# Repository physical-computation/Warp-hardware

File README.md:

**The Warp hardware platform integrates 21 sensors in a complete system that is 3.6cmx3.3cm**
- - - - 

# Warp
Warp is a hardware platform for efficient multi-modal sensing with adaptive approximation. The hardware contains 11 sensor integrated circuits (ICs) and a total of 21 different sensors. The design includes circuit-level facilities for trading sensor accuracy for power dissipation, and circuit-level facilities for trading sensor communication reliability for power dissipation. The sensors in Warp cover eight sensing modalities: temperature, pressure, 3-axis acceleration, 3-axis angular velocity, 3-axis magnetic flux density, humidity, infrared, color/light (615nm, 525nm, 465nm).

## Prerequisites
We provide the hardware design files in the Eagle CAD format. You can use the free version of Eagle for MacOS, Linux, Windows to view the files. The design is a 10-layer PCB. You will need the full version of Eagle to make modifications. [For academics, the full version of Eagle (Eagle Professional) is completely free](https://knowledge.autodesk.com/support/eagle/learn-explore/caas/sfdcarticles/sfdcarticles/Eagle-Education.html). For non-university hobbyists, Eagle is relatively inexpensive and can also be purchased on a month-at-a-time subscription.

We also provide the hardware design files as Gerbers. You can use any of the numerous free Gerber viewers to view the design.

## Getting boards manufactured
The repository contains detailed instructions for getting the boards manufactured. We provide a pre-populated BOM file with part numbers for purchasing the components from Mouser. Before getting your own boards manufactured, it is worthwhile getting in touch with us for a brief discussion of things to be careful about in providing instructions to your board assembly house.

## Adapting the designs
We license the Warp hardware designs under a BSD license. See details in [LICENSE.txt](https://github.com/physical-computation/Warp-hardware/blob/master/LICENSE.txt).

## Generating Gerbers for manufacturing
The repository comes with the Gerber files pre-generated. You can generate your own Gerber files and drill files for manufacturing using Eagle.

## Getting boards assembled
Basic [BOM](https://github.com/physical-computation/Warp-hardware/blob/master/revA/bom/mouser/warp-revA-bom.xlsx) (uses Mouser for components).

# Implementation and Debug

# Mechanical CAD Models for Board and Enclosures
The repository also contains a mechanical CAD model for the board and designs for enclosures, in Autodesk Fusion 360 format. [For academics, the full version of Autodesk Fusion 360 is completely free](https://www.autodesk.co.uk/products/fusion-360/students-teachers-educators). For non-university hobbyists, Fusion 360 is relatively inexpensive and can be purchased on a month-at-a-time subscription.

## Getting firmware
You can obtain baseline firmware for the Warp platform from the [Warp firmware](https://github.com/physical-computation/Warp-firmware) repository.

## Bugs
See the GitHub issues for a complete list. Before getting your own boards manufactured, it is worthwhile getting in touch with us for a brief discussion of things to be careful about in providing instructions to your board assembly house and hints for getting the firmware running on Warp for the first time.

### If you use Warp in your research, please cite it as:
Phillip Stanley-Marbell and Martin Rinard. “A Hardware Platform for Efficient Multi-Modal Sensing with Adaptive Approximation”. ArXiv e-prints (2018). arXiv:1804.09241.

**BibTeX:**
```
@ARTICLE{1804.09241,
	author = {Stanley-Marbell, Phillip and Rinard, Martin},
	title = {A Hardware Platform for Efficient Multi-Modal 
	Sensing with Adaptive Approximation},
	journal = {ArXiv e-prints},
	archivePrefix = {arXiv},
	eprint = {1804.09241},
	year = 2018,
}
```
Phillip Stanley-Marbell and Martin Rinard. “Warp: A Hardware Platform for Efficient Multi-Modal Sensing with Adaptive Approximation”. IEEE Micro, Volume 40 , Issue 1 , Jan.-Feb. 2020.

**BibTeX:**
```
@ARTICLE{8959350,
	author = {P. {Stanley-Marbell} and M. {Rinard}}, 
	title = {Warp: A Hardware Platform for Efficient Multi-Modal
	Sensing with Adaptive Approximation},
	journal = {IEEE Micro},
	year = {2020}, 
	volume = {40}, 
	number = {1}, 
	pages = {57-66}, 
	ISSN = {1937-4143}, 
	month = {Jan},
}
```
### Acknowledgements
This research is supported by an Alan Turing Institute award TU/B/000096 under EPSRC grant EP/N510129/1, by Royal Society grant RG170136, and by EPSRC grants EP/P001246/1 and EP/R022534/1.

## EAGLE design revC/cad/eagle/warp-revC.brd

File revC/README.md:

## Overview
Warp Revision C adds support for a replaceable battery on a JST-PH connector, battery charging via USB, and a new Bluetooth LE module.

## Switch Settings
- Switch S1: Position 1: OFF; Position 2: OFF
- Switch S2: Position 1, OFF; Position 2: ON

## Battery
JST-PH connector. Polarity: When looking at the top surface of the Warp Revision C board (surface with logo and serial number), the red (positive) conductor will be on the left and the black (negative) conductor will be on the right:

## Connecting via Bluetooth LE
You can connect to Warp using the BGX Commander app on [iOS](https://apps.apple.com/us/app/bgxcommander/id1350920514) and [Android](https://play.google.com/store/apps/details?id=com.silabs.bgxcommander&hl=en_GB&gl=US) (and using similar facilities on Linux, Windows, and macOS):

Once connected, select your Warp from the list of devices and you get a terminal into the Warp prompt (or if your firmware is compiled to enable `WARP_BUILD_BOOT_TO_CSVSTREAM`, you get the CSV stream):

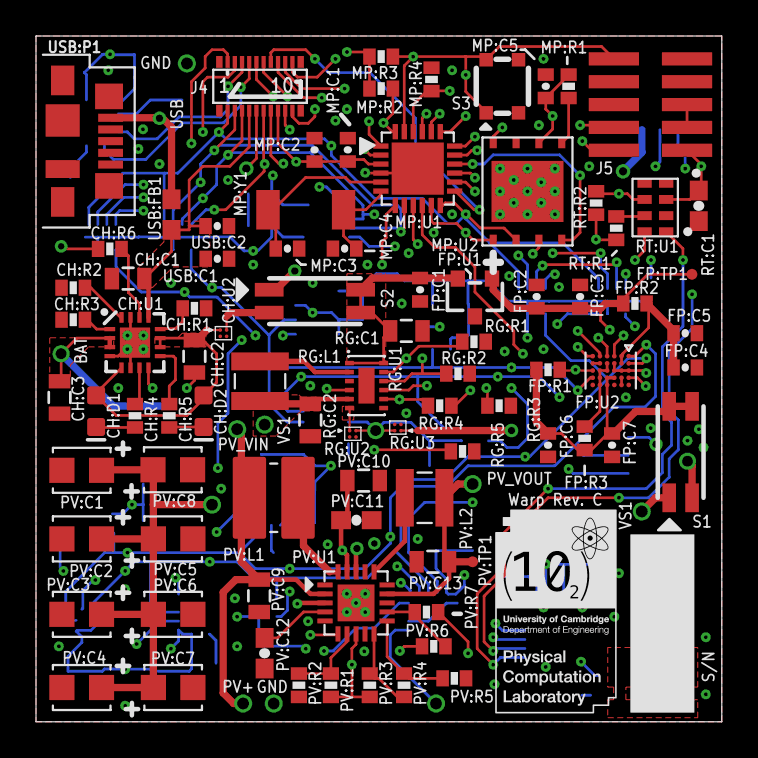
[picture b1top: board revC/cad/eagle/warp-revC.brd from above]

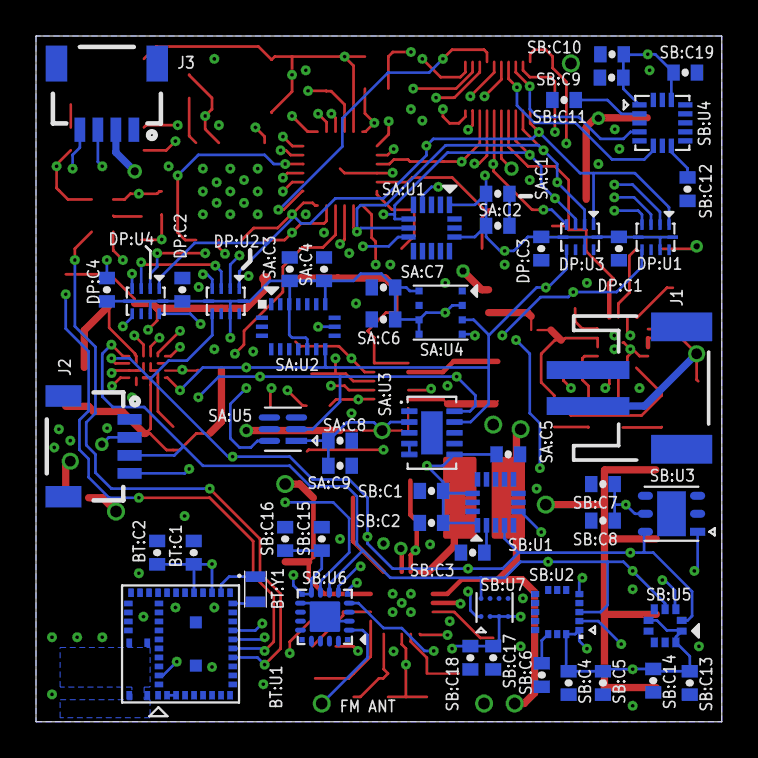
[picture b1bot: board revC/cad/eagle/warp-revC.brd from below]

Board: 10 copper layers, 38.1 x 38.1 mm, 141 parts (55 on the bottom side), 73 nets.

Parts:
BT:C1: 0.1uF; 0402-CAP
BT:C2: 1uF; 0402-CAP
BT:U1: BGX13S22GA-V21R; BGX13S
BT:Y1: IQXC-25
CH:C1: 1uF; 0805
CH:C2, CH:C3: 4.7uF; 0805
CH:D1: Green; LED-0603
CH:D2: Red; LED-0603
CH:R1: 2.94k; 0402-RES
CH:R2: 4.32k; 0402-RES
CH:R3: 10k; 0402-RES
CH:R4, CH:R5: 2k; 0402-RES
CH:R6: 56.2k; 0402-RES
CH:U1: BQ24230VQFN; PVQFN-N16
CH:U2: MAX40200; DSBGA
DP:C1, DP:C2, DP:C3, DP:C4: 0.1uF; 0402-CAP
DP:U1, DP:U2, DP:U3, DP:U4: ISL23415UTQFN; ISL23415
FP:C1, FP:C2: 1uF; 0402-CAP
FP:C3, FP:C4, FP:C7: 0.1uF; 0402-CAP
FP:C5, FP:C6: 10uF; 0402-CAP
FP:R1, FP:R3: 10k; 0402-RES
FP:R2: 100; 0402-RES
FP:TP1: TPSTP06R; TP06R
FP:U1: MCP1811AT-012/TTSOT-23-3; SOT23-3
FP:U2: ICE40UP5K-UWG30; LATTICE-WLCSP-30
J1: JST-2-SMD
J2, J3: QIIC connector; 1X04_1MM_RA
J4: DF40FC-20DP-0.4V(51); DF40C-20DP-0.4V(51)
J5: FTSH-105-01-XXX-DV-K
MP:C1, MP:C5: 0.1uF; 0402-CAP
MP:C2: 4.7uF; 0402-CAP
MP:C3, MP:C4: 33pF; 0402-CAP
MP:R1, MP:R2, MP:R4: 10k; 0402-RES
MP:R3: 4.7k; 0402-RES
MP:U1: MKL03Z32VFK4RQFN24; MKL03Z32VFK4R
MP:U2: AT45DB641E-MHN-Y; UDFN
MP:Y1: CM519-SMD; CM519
PV:C1, PV:C2, PV:C3, PV:C4, PV:C5, PV:C6, PV:C7, PV:C8: CPX3225A7552D; CPX3225A752D
PV:C9, PV:C10: 4.7uF; 0805
PV:C11: 0.1uF; 0603-CAP
PV:C12: 10nF; 0603-CAP
PV:C13: 22uF; 0805
PV:L1: 22uH; WE-TPC_3816
PV:L2: 10uH; WE-TPC_2811/2813_OLD
PV:R1: 4.02M; 0402-RES
PV:R2: 9.09M; 0402-RES
PV:R3: 1.3M; 0402-RES
PV:R4: 5.36M; 0402-RES
PV:R5: 6.49M; 0402-RES
PV:R6: 8.87M; 0402-RES
PV:R7: 4.22M; 0402-RES
PV:TP1: TPSTP06R; TP06R
PV:U1: BQ25570PVQFN; BQ25570
RG:C1, RG:C2: 10uF; 0805
RG:L1: 2.2uH; WE-TPC_2828_OLD
RG:R1, RG:R2, RG:R3, RG:R4, RG:R5: 2M; 0402-RES
RG:U1: TPS6274XWSON; WSON-12
RG:U2, RG:U3: MAX40200; DSBGA
RT:C1: 0.1uF; 0603-CAP
RT:R1, RT:R2: 10k; 0402-RES
RT:U1: RV-8803-C7_RTC; RV-C7
S1, S2: CHS-02_SWITCH
S3: EVPAYG0BAEVPAYG0BA; EVPAYG0BA
SA:C1, SA:C3, SA:C6, SA:C8: 0.1uF; 0402-CAP
SA:C2, SA:C4, SA:C7, SA:C9: 1uF; 0402-CAP
SA:C5: 4.7uF; 0402-CAP
SA:U1: ADXL362
SA:U2: BMX055
SA:U3: CCS811; SON60P270X400X110-11N
SA:U4: BME680LGA; BME680
SA:U5: TCS34725FN; TCS3772
SB:C1, SB:C3, SB:C4, SB:C7, SB:C9, SB:C11, SB:C12, SB:C13, SB:C16, SB:C17, SB:C19: 0.1uF; 0402-CAP
SB:C2, SB:C8, SB:C18: 1uF; 0402-CAP
SB:C5: 10uF; 0402-CAP
SB:C6: 10nF; 0402-CAP
SB:C10, SB:C14: 4.7uF; 0402-CAP
SB:C15: 22nF; 0402-CAP
SB:U1: MMA8451Q
SB:U2: L3GD20H
SB:U3: SI7021
SB:U4: FXOS8700CQ; QFN16
SB:U5: LPS25H
SB:U6: SI4705
SB:U7: HDC1000
USB:C1: 4.7uF; 0402-CAP
USB:C2: 0.1uF; 0402-CAP
USB:FB1: 600R/1A; 0603
USB:P1: MOLEX_USB_47346-0001MICRO_USB_B; USB-B-MICRO-SMD

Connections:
ADXL362_SPI_CS: MP:U1.P$15, SA:U1.P$8
BAT: CH:C3.1, CH:U1.2, CH:U1.3, J1.2
BGX13S_!RST: BT:U1.44, MP:U1.P$7
BOOST_VBAT: PV:C1.+, PV:C2.+, PV:C3.+, PV:C4.+, PV:C5.+, PV:C6.+, PV:C7.+, PV:C8.+, PV:U1.18
BT:N$1: BT:U1.21, BT:Y1.1
BT:N$2: BT:U1.19, BT:Y1.2
BT:N$3: BT:U1.2, BT:U1.3
CH:BQ24230_OUT: CH:C2.1, CH:D1.A, CH:D2.A, CH:U1.5, CH:U1.10, CH:U1.11, CH:U2.A1
CH:N$1: CH:R2.2, CH:U1.16
CH:N$2: CH:R1.2, CH:U1.12
CH:N$3: CH:R4.1, CH:U1.7
CH:N$4: CH:R3.2, CH:U1.1
CH:N$5: CH:R5.1, CH:U1.9
CH:N$6: CH:D1.C, CH:R4.2
CH:N$7: CH:D2.C, CH:R5.2
CH:N$8: CH:R6.2, CH:U1.14
CHARGE_VOUT: CH:U2.A2, S2.2
CLK32K: MP:U1.P$21, SB:U6.P$9
CRESET_B: FP:R1.1, FP:U2.F3, J4.P$17
FP:ICE40_VCC_PLL: FP:C4.1, FP:C5.1, FP:R2.1, FP:U2.B1, FP:U2.B2
FP:VCC_1V2: FP:C2.1, FP:C3.1, FP:R2.2, FP:TP1.TP, FP:U1.1, FP:U2.A3, FP:U2.B3, FP:U2.C2, FP:U2.C3
FP:VCC_SHUNT: FP:R3.1, FP:U2.D2, FP:U2.D3, FP:U2.E3, FP:U2.E4, FP:U2.E5
FPGA_CS: FP:U2.C1, J4.P$7, MP:U1.P$13
FPGA_VS: FP:C6.1, FP:C7.1, FP:R1.2, FP:R3.2, FP:U2.C4, FP:U2.D4, FP:U2.D5, S1.1', S1.2'
GND: BT:C1.2, BT:C2.2, BT:U1.1, BT:U1.4, BT:U1.5, BT:U1.20, BT:U1.31, BT:U1.45, BT:U1.46, BT:U1.47, BT:U1.48, BT:U1.49, BT:U1.50, BT:U1.51, CH:C1.2, CH:C2.2, CH:C3.2, CH:R1.1, CH:R2.1, CH:R3.1, CH:R6.1, CH:U1.4, CH:U1.6, CH:U1.8, CH:U1.15, CH:U1.EP, CH:U2.B2, DP:C1.2, DP:C2.2, DP:C3.2, DP:C4.2, DP:U1.9, DP:U2.9, DP:U3.9, DP:U4.9, FP:C1.2, FP:C2.2, FP:C3.2, FP:C4.2, FP:C5.2, FP:C6.2, FP:C7.2, FP:U1.3, FP:U2.B4, FP:U2.B5, FP:U2.E2, FP:U2.F2, J1.1, J2.1, J3.1, J4.P$20, J5.3, J5.5, MP:C1.2, MP:C2.2, MP:C3.2, MP:C4.2, MP:C5.2, MP:R4.2, MP:U1.P$4, MP:U1.P$PAD, MP:U2.7, MP:U2.9, PV:C1.-, PV:C2.-, PV:C3.-, PV:C4.-, PV:C5.-, PV:C6.-, PV:C7.-, PV:C8.-, PV:C9.2, PV:C10.2, PV:C11.2, PV:C12.2, PV:C13.2, PV:R2.1, PV:R5.1, PV:R7.1, PV:U1.1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
I2C0_SCL/UART_TX: BT:U1.14, J4.P$5, MP:U1.P$17, RT:U1.8
I2C0_SDA/UART_RX: BT:U1.13, J4.P$6, MP:U1.P$18, RT:U1.1
I2C1_SCL: DP:U1.6, FP:U2.A4, J3.4, J4.P$1, SA:U2.P$9, SA:U3.10, SA:U4.4, SA:U5.2
I2C1_SDA: DP:U3.6, FP:U2.F4, J3.3, J4.P$2, SA:U2.P$11, SA:U3.9, SA:U4.3, SA:U5.6
I2C2_SCL: DP:U2.6, FP:U2.A2, J2.4, J4.P$3, SB:U1.4, SB:U2.2, SB:U3.6, SB:U4.P$4, SB:U5.2, SB:U6.P$7, SB:U7.A1
I2C2_SDA: DP:U4.6, FP:U2.A1, J2.3, J4.P$4, SB:U1.6, SB:U2.3, SB:U3.1, SB:U4.P$6, SB:U5.4, SB:U6.P$8, SB:U7.A2
ISL23415_SPI_CS: DP:U1.4, DP:U2.4, DP:U3.4, DP:U4.4, J4.P$16, MP:U1.P$20
MP:AT45DB321F_SPI_CS: MP:U1.P$16, MP:U2.4
MP:EXTAL0: MP:C3.1, MP:U1.P$5, MP:Y1.P$1
MP:N$4: MP:R1.1, MP:U2.5
MP:XTAL0: MP:C4.1, MP:U1.P$6, MP:Y1.P$2
PV:LBOOST: PV:L1.2, PV:U1.20
PV:LBUCK: PV:L2.2, PV:U1.16
PV:OK_HYST: PV:R3.1, PV:R4.2, PV:U1.10
PV:OK_PROG: PV:R4.1, PV:R5.2, PV:U1.11
PV:VBAT_OV: PV:R1.1, PV:R2.2, PV:U1.7
PV:VOUT_SET: PV:R6.1, PV:R7.2, PV:U1.12
PV:VRDIV: PV:R1.2, PV:R3.2, PV:R6.2, PV:U1.8
PV:VREF_SAMP: PV:C12.1, PV:U1.4
PV:VSTOR: PV:C10.1, PV:C11.1, PV:U1.3, PV:U1.6, PV:U1.19
PV_VIN: J4.P$15, PV:C9.1, PV:L1.1, PV:U1.2
PV_VOUT: PV:C13.1, PV:L2.1, PV:TP1.TP, PV:U1.14, S2.1
REG_CTRL: MP:U1.P$19, RG:R5.2, RG:U1.4
REG_VIN: FP:C1.1, FP:U1.2, RG:C1.1, RG:U1.1, RG:U1.12, S2.1', S2.2'
REG_VSEL1: MP:U1.P$1, RG:R1.2, RG:U1.11
REG_VSEL2: MP:U1.P$2, RG:R2.2, RG:U1.10
REG_VSEL3: MP:U1.P$9, RG:R3.2, RG:U1.9
REG_VSEL4: MP:U1.P$10, RG:R4.2, RG:U1.8
RG:LOAD: RG:U1.6, RG:U2.A1
RG:SW: RG:L1.1, RG:U1.2
RT:N$3: RT:R1.1, RT:U1.7
RTC_!INT!/RESET_B: J4.P$10, J5.10, MP:R3.1, MP:U1.P$23, RT:R2.1, RT:U1.6, S3.A, S3.A'
SA:N$2: SA:U3.4, SA:U3.5
SB:CAP: SB:C6.1, SB:U2.14
SB:N$1: SB:C3.1, SB:U1.2
SB:N$2: SB:C11.1, SB:U4.P$2
SB:N$3: SB:C12.1, SB:U4.P$8
SI4705_!RST: MP:U1.P$14, SB:U6.P$5
SPI_MISO/UART_RTS: BT:U1.16, DP:U1.2, DP:U2.2, DP:U3.2, DP:U4.2, FP:U2.F1, J4.P$12, MP:U1.P$8, MP:U2.8, SA:U1.P$7
SPI_MOSI/UART_CTS: BT:U1.15, DP:U1.3, DP:U2.3, DP:U3.3, DP:U4.3, FP:U2.E1, J4.P$13, MP:U1.P$11, MP:U2.1, SA:U1.P$6
SPI_SCK: DP:U1.1, DP:U2.1, DP:U3.1, DP:U4.1, FP:U2.D1, J4.P$11, MP:U1.P$12, MP:U2.2, SA:U1.P$4
SWD_CLK: J4.P$9, J5.4, MP:R4.1, MP:U1.P$22
SWD_DIO: J4.P$8, J5.2, MP:R2.1, MP:U1.P$24
USB:VBUS: USB:FB1.2, USB:P1.1
USB_5V: CH:C1.1, CH:U1.13, J4.P$14, USB:C1.1, USB:C2.1, USB:FB1.1
VCC_QIIC: J2.2, J3.2, RG:U3.A1
VS1: J4.P$18, J5.1, MP:C1.1, MP:C2.1, MP:C5.1, MP:R1.2, MP:R2.2, MP:R3.2, MP:U1.P$3, MP:U2.3, MP:U2.6, RG:C2.1, RG:L1.2, RG:U1.5, RT:C1.1, RT:R1.2, RT:R2.2, RT:U1.3, S1.1
VS2: BT:C1.1, BT:C2.1, BT:U1.22, BT:U1.24, DP:C1.1, DP:C2.1, DP:C3.1, DP:C4.1, DP:U1.5, DP:U1.8, DP:U1.10, DP:U2.5, DP:U2.8, DP:U2.10, DP:U3.5, DP:U3.8, DP:U3.10, DP:U4.5, DP:U4.8, DP:U4.10, J4.P$19, RG:U2.A2, RG:U3.A2, S1.2, SA:C1.1, SA:C2.1, SA:C3.1, SA:C4.1, SA:C5.1, SA:C6.1, SA:C7.1, SA:C8.1, SA:C9.1, SA:U1.P$1, SA:U1.P$14, SA:U2.P$3, SA:U2.P$7, SA:U2.P$13, SA:U3.2, SA:U3.6, SA:U4.2, SA:U4.5, SA:U4.6, SA:U4.8, SA:U5.1, SB:C1.1, SB:C2.1, SB:C4.1, SB:C5.1, SB:C7.1, SB:C8.1, SB:C9.1, SB:C10.1, SB:C13.1, SB:C14.1, SB:C15.1, SB:C16.1, SB:C17.1, SB:C18.1, SB:C19.1, SB:U1.1, SB:U1.14, SB:U2.1, SB:U2.5, SB:U2.16, SB:U3.5, SB:U4.P$1, SB:U4.P$14, SB:U5.1, SB:U5.6, SB:U5.10, SB:U6.P$10, SB:U6.P$11, SB:U7.B1, SB:U7.C1, SB:U7.D1

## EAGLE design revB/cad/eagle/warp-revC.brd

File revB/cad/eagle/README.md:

# Warp revision B, Eagle CAD files

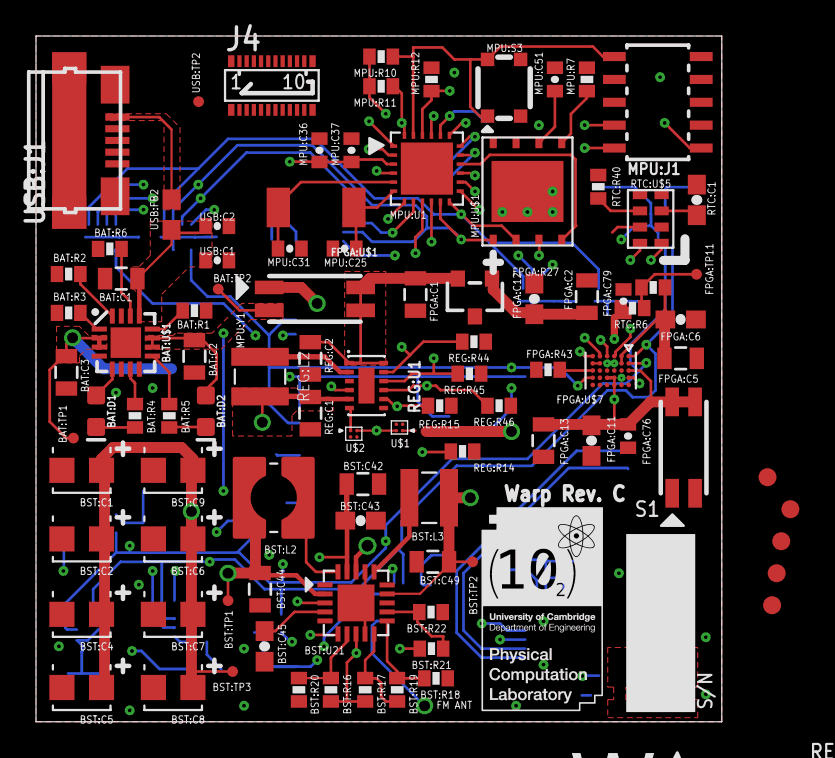
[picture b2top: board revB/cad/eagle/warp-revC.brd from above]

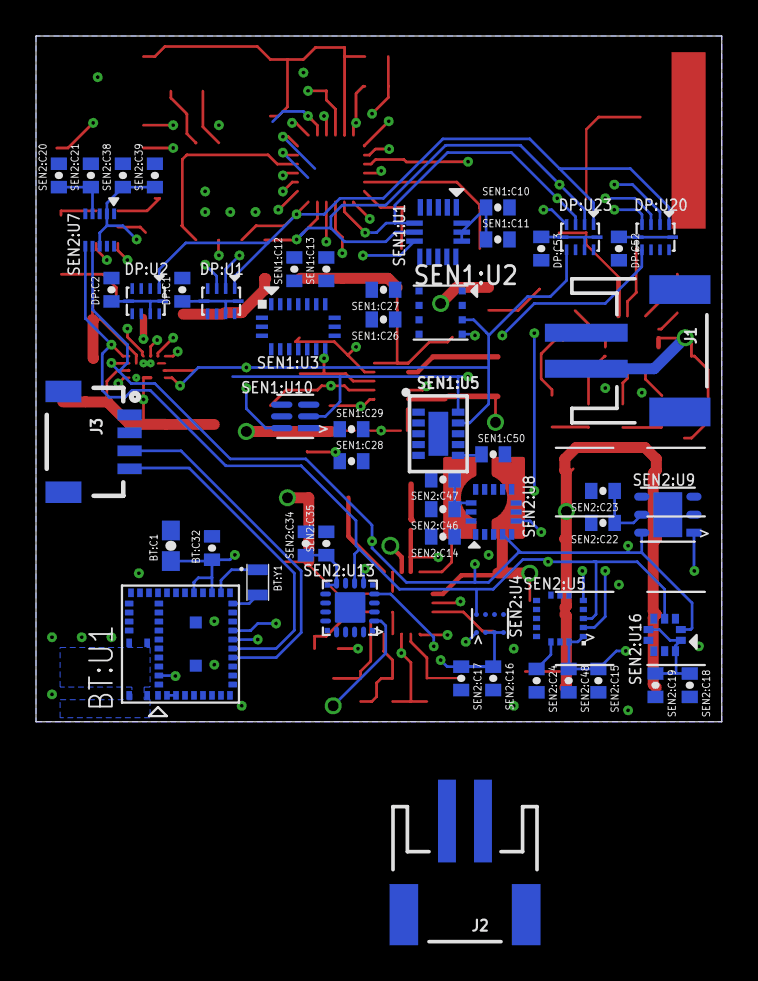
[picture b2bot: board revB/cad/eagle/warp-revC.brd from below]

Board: 10 copper layers, 38.1 x 38.1 mm, 150 parts (54 on the bottom side), 71 nets.

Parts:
BAT:C1: 1uF; 0805
BAT:C2, BAT:C3: 4.7uF; 0805
BAT:D1, BAT:D2: LED-0603
BAT:R1: 2.94k; 0402-RES
BAT:R2: 4.32k; 0402-RES
BAT:R3: 10k; 0402-RES
BAT:R4, BAT:R5: 4.7k; 0402-RES
BAT:R6: 56.2k; 0402-RES
BAT:TP1, BAT:TP2: TPSTP06R; TP06R
BAT:U$1: BQ24230VQFN; PVQFN-N16
BST:C1, BST:C2, BST:C4, BST:C5, BST:C6, BST:C7, BST:C8, BST:C9: CPX3225A7552D; CPX3225A752D
BST:C42, BST:C44: 4.7uF; 0805
BST:C43: 0.1uF; 0603-CAP
BST:C45: 10nF; 0603-CAP
BST:C49: 22uF; 0805
BST:L2: 22uH; WE-TPC_3816
BST:L3: 10uH; WE-TPC_2811/2813_OLD
BST:R16: 4.02M; 0402-RES
BST:R17: 1.3M; 0402-RES
BST:R18: 6.49M; 0402-RES
BST:R19: 5.36M; 0402-RES
BST:R20: 9.09M; 0402-RES
BST:R21: 8.87M; 0402-RES
BST:R22: 4.22M; 0402-RES
BST:TP1, BST:TP2, BST:TP3: TPSTP06R; TP06R
BST:U21: BQ25570PVQFN; BQ25570
BT:C1: 1uF; 0603-CAP
BT:C32: 0.1uF; 0402-CAP
BT:U1: BGX13S
BT:Y1: IQXC-25
DP:C1, DP:C2, DP:C52, DP:C53: 0.1uF; 0402-CAP
DP:U1, DP:U2, DP:U20, DP:U23: ISL23415UTQFN; ISL23415
FD1, FD2, FD3, FD4, FD5: FIDUCIAL1X2; FIDUCIAL-1X2
FPGA:C1, FPGA:C2, FPGA:C13: 1uF; 0805
FPGA:C5: 10uF; 0805
FPGA:C6, FPGA:C11, FPGA:C12: 0.1uF; 0603-CAP
FPGA:C76, FPGA:C79: 10nF; 0402-CAP
FPGA:R27: 100; 0402-RES
FPGA:R43: 10k; 0402-RES
FPGA:TP11: TPSTP06R; TP06R
FPGA:U$1: MCP1811AT-012/TTSOT-23-3; SOT23-3
FPGA:U$7: ICE40UP5K-UWG30; LATTICE-WLCSP-30
J1, J2: JST-2-SMD
J3: QIIC connector; 1X04_1MM_RA
J4: DF40FC-20DP-0.4V(51); DF40C-20DP-0.4V(51)
MPU:C25, MPU:C31: 33pF; 0402-CAP
MPU:C36: 4.7uF (pol); 0402-CAP
MPU:C37, MPU:C51: 0.1uF; 0402-CAP
MPU:J1: CORTEX_DEBUG_SMD; SAMTECH_FTSH-105-01
MPU:R7, MPU:R11, MPU:R12: 10k; 0402-RES
MPU:R10: 4.7k; 0402-RES
MPU:S3: EVPAYG0BAEVPAYG0BA; EVPAYG0BA
MPU:U1: MKL03Z32VFK4RQFN24; MKL03Z32VFK4R
MPU:U$1: AT45DB641E; UDFN
MPU:Y1: CM519-SMD; CM519
REG:C1, REG:C2: 10uF; 0805
REG:L2: 2.2uH; WE-TPC_2828_OLD
REG:R14, REG:R15, REG:R44, REG:R45, REG:R46: 2M; 0402-RES
REG:U1: TPS6274XWSON; WSON-12
RTC:C1: 0.1uF; 0603-CAP
RTC:R6, RTC:R40: 10k; 0402-RES
RTC:U$5: RV-8803-C7_RTC; RV-C7
S1, S3: CHS-02_SWITCH
SEN1:C10, SEN1:C12, SEN1:C26, SEN1:C28, SEN2:C14, SEN2:C16, SEN2:C18, SEN2:C20, SEN2:C21, SEN2:C23, SEN2:C34, SEN2:C38, SEN2:C46, SEN2:C48: 0.1uF; 0402-CAP
SEN1:C11, SEN1:C13, SEN1:C27, SEN1:C29, SEN2:C17, SEN2:C22, SEN2:C39, SEN2:C47: 1uF; 0402-CAP
SEN1:C50, SEN2:C19: 4.7uF; 0402-CAP
SEN1:U1: ADXL362
SEN1:U2: BME680LGA; BME680
SEN1:U3: BMX055
SEN1:U5: CCS811; LGA10
SEN1:U10: TCS34725FN; TCS3772
SEN2:C15: 10uF; 0402-CAP
SEN2:C24: 10nF (25V); 0402-CAP
SEN2:C35: 22nF; 0402-CAP
SEN2:U4: HDC1000
SEN2:U5: L3GD20H
SEN2:U7: MAG3110
SEN2:U8: MMA8451Q
SEN2:U9: SI7021
SEN2:U13: SI4705
SEN2:U16: LPS25H
U$1, U$2: MAX40200; DSBGA
USB:C1: 4.7uF (pol); 0402-CAP
USB:C2: 0.1uF; 0402-CAP
USB:FB2: 600R/1A; 0603
USB:J1: J_USB_MICROAB_HIROSE_ZX62-AB-5PA
USB:TP2: TPSTP06R; TP06R

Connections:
ADXL362_SPI_CS: J4.P$18, MPU:U1.P$15, SEN1:U1.P$8
BAT: BAT:C3.1, BAT:TP1.TP, BAT:U$1.2, BAT:U$1.3, J1.2
BAT:N$1: BAT:R2.2, BAT:U$1.16
BAT:N$2: BAT:R1.2, BAT:U$1.12
BAT:N$3: BAT:R4.1, BAT:U$1.7
BAT:N$4: BAT:R3.2, BAT:U$1.1
BAT:N$5: BAT:R5.1, BAT:U$1.9
BAT:N$6: BAT:D1.C, BAT:R4.2
BAT:N$7: BAT:D2.C, BAT:R5.2
BAT:N$8: BAT:R6.2, BAT:U$1.14
BGX13S_!RST: BT:U1.44, J4.P$20, MPU:U1.P$7
BOOST_VBAT: BST:C1.+, BST:C2.+, BST:C4.+, BST:C5.+, BST:C6.+, BST:C7.+, BST:C8.+, BST:C9.+, BST:TP3.TP, BST:U21.18
BOOST_VOUT: BST:C49.1, BST:L3.2, BST:TP2.TP, BST:U21.14, S3.1
BST:LBOOST: BST:L2.2, BST:U21.20
BST:LBUCK: BST:L3.1, BST:U21.16
BST:OK_HYST: BST:R17.1, BST:R19.2, BST:U21.10
BST:OK_PROG: BST:R18.2, BST:R19.1, BST:U21.11
BST:VBAT_OV: BST:R16.1, BST:R20.2, BST:U21.7
BST:VOUT_SET: BST:R21.1, BST:R22.2, BST:U21.12
BST:VRDIV: BST:R16.2, BST:R17.2, BST:R21.2, BST:U21.8
BST:VREF_SAMP: BST:C45.1, BST:U21.4
BST:VSTOR: BST:C42.1, BST:C43.1, BST:U21.3, BST:U21.6, BST:U21.19
BT:N$1: BT:U1.21, BT:Y1.1
BT:N$2: BT:U1.19, BT:Y1.2
BT:N$3: BT:U1.2, BT:U1.3
CHARGE_VOUT: BAT:C2.1, BAT:D1.A, BAT:D2.A, BAT:TP2.TP, BAT:U$1.5, BAT:U$1.10, BAT:U$1.11, S3.2
CLK32K: MPU:U1.P$21, SEN2:U13.P$9
DP:ISL23415_SPI_CS: DP:U1.4, DP:U2.4, DP:U20.4, DP:U23.4
FPGA:CRESET_B: FPGA:R43.1, FPGA:U$7.F3
FPGA:ICE40_VCC_PLL: FPGA:C5.1, FPGA:C6.1, FPGA:R27.1, FPGA:U$7.B1, FPGA:U$7.B2
FPGA:VCC_1V2: FPGA:C2.1, FPGA:C12.1, FPGA:C79.1, FPGA:R27.2, FPGA:TP11.TP, FPGA:U$1.1, FPGA:U$7.C2
FPGA_CS: FPGA:U$7.C1, MPU:U1.P$13
FPGA_VS: FPGA:C11.1, FPGA:C13.1, FPGA:C76.1, FPGA:R43.2, FPGA:U$7.A3, FPGA:U$7.C4, FPGA:U$7.C5, FPGA:U$7.D2, FPGA:U$7.D4, S1.1', S1.2'
GND: BAT:C1.2, BAT:C2.2, BAT:C3.2, BAT:R1.1, BAT:R2.1, BAT:R3.1, BAT:R6.1, BAT:U$1.4, BAT:U$1.6, BAT:U$1.8, BAT:U$1.15, BAT:U$1.EP, BST:C1.-, BST:C2.-, BST:C4.-, BST:C5.-, BST:C6.-, BST:C7.-, BST:C8.-, BST:C9.-, BST:C42.2, BST:C43.2, BST:C44.2, BST:C45.2, BST:C49.2, BST:R18.1, BST:R20.1, BST:R22.1, BST:U21.1, BST:U21.5, BST:U21.9, BST:U21.15, BST:U21.17, BST:U21.21, BT:C1.2, BT:C32.2, BT:U1.1, BT:U1.4, BT:U1.5, BT:U1.20, BT:U1.31, BT:U1.45, BT:U1.46, BT:U1.47, BT:U1.48, BT:U1.49, BT:U1.50, BT:U1.51, DP:C1.2, DP:C2.2, DP:C52.2, DP:C53.2, DP:U1.9, DP:U2.9, DP:U20.9, DP:U23.9, FPGA:C1.2, FPGA:C2.2, FPGA:C5.2, FPGA:C6.2, FPGA:C11.2, FPGA:C12.2, FPGA:C13.2, FPGA:C76.2, FPGA:C79.2, FPGA:U$1.3, FPGA:U$7.B4, FPGA:U$7.E2, FPGA:U$7.F2, J1.1, J2.1, J3.1, J4.P$1, MPU:C25.2, MPU:C31.2, MPU:C36.2, MPU:C37.2, MPU:C51.2, MPU:J1.3, MPU:J1.5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
I2C0_SCL/UART_TX: BT:U1.14, J3.4, J4.P$11, MPU:U1.P$17, RTC:U$5.8
I2C0_SDA/UART_RX: BT:U1.13, J3.3, J4.P$12, MPU:U1.P$18, RTC:U$5.1
I2C1_SCL: DP:U20.6, FPGA:U$7.A4, J4.P$13, SEN1:U2.4, SEN1:U3.P$9, SEN1:U5.10, SEN1:U10.P$2
I2C1_SDA: DP:U23.6, FPGA:U$7.F4, J4.P$14, SEN1:U2.3, SEN1:U3.P$11, SEN1:U5.9, SEN1:U10.P$6
I2C2_SCL: DP:U1.6, FPGA:U$7.A2, J4.P$15, SEN2:U4.A1, SEN2:U5.P$2, SEN2:U7.P$7, SEN2:U8.P$4, SEN2:U9.P$6, SEN2:U13.P$7, SEN2:U16.P$2
I2C2_SDA: DP:U2.6, FPGA:U$7.A1, J4.P$16, SEN2:U4.A2, SEN2:U5.P$3, SEN2:U7.P$6, SEN2:U8.P$6, SEN2:U9.P$1, SEN2:U13.P$8, SEN2:U16.P$4
ISL23415_SPI_CS: J4.P$17, MPU:U1.P$20
MPU:AT45DB321F_SPI_CS: MPU:U1.P$16, MPU:U$1.4
MPU:EXTAL0: MPU:C31.1, MPU:U1.P$5, MPU:Y1.P$1
MPU:N$4: MPU:R7.1, MPU:U$1.5
MPU:XTAL0: MPU:C25.1, MPU:U1.P$6, MPU:Y1.P$2
PV_VS: BST:C44.1, BST:L2.1, BST:TP1.TP, BST:U21.2, J2.2, J4.P$4
REG:SW: REG:L2.1, REG:U1.2
REG_CTRL: MPU:U1.P$19, REG:R14.2, REG:U1.4
REG_LOAD: REG:U1.6, U$2.A1
REG_VIN: FPGA:C1.1, FPGA:U$1.2, REG:C2.1, REG:U1.1, REG:U1.12, S3.1', S3.2'
REG_VSEL1: MPU:U1.P$1, REG:R44.2, REG:U1.11
REG_VSEL2: MPU:U1.P$2, REG:R45.2, REG:U1.10
REG_VSEL3: MPU:U1.P$9, REG:R46.2, REG:U1.9
REG_VSEL4: MPU:U1.P$10, REG:R15.2, REG:U1.8
RTC:N$3: RTC:R6.1, RTC:U$5.7
RTC_!INT!/RESET_B: J4.P$7, MPU:J1.10, MPU:R10.1, MPU:S3.A, MPU:S3.A', MPU:U1.P$23, RTC:R40.1, RTC:U$5.6
SEN1:N$7: SEN1:U5.4, SEN1:U5.5
SEN2:CAP: SEN2:C24.1, SEN2:U5.P$14
SEN2:N$1: SEN2:C14.1, SEN2:U8.P$2
SEN2:N$17: SEN2:C20.1, SEN2:C21.1, SEN2:U7.P$1, SEN2:U7.P$4
SI4705_!RST: J4.P$19, MPU:U1.P$14, SEN2:U13.P$5
SPI_MISO/UART_RTS: BT:U1.16, DP:U1.2, DP:U2.2, DP:U20.2, DP:U23.2, FPGA:U$7.F1, J4.P$9, MPU:U1.P$11, MPU:U$1.1, SEN1:U1.P$7
SPI_MOSI/UART_CTS: BT:U1.15, DP:U1.3, DP:U2.3, DP:U20.3, DP:U23.3, FPGA:U$7.E1, J4.P$10, MPU:U1.P$8, MPU:U$1.8, SEN1:U1.P$6
SPI_SCK: DP:U1.1, DP:U2.1, DP:U20.1, DP:U23.1, FPGA:U$7.D1, J4.P$8, MPU:U1.P$12, MPU:U$1.2, SEN1:U1.P$4
SWD_CLK: J4.P$6, MPU:J1.4, MPU:R12.1, MPU:U1.P$22
SWD_DIO: J4.P$5, MPU:J1.2, MPU:R11.1, MPU:U1.P$24
USB:VBUS: USB:FB2.2, USB:J1.P$1
USB_5V: BAT:C1.1, BAT:U$1.13, J4.P$2, USB:C1.1, USB:C2.1, USB:FB2.1, USB:TP2.TP
VCC_QIIC: J3.2, U$1.A1
VS1: MPU:C36.1, MPU:C37.1, MPU:C51.1, MPU:J1.1, MPU:R7.2, MPU:R10.2, MPU:R11.2, MPU:U1.P$3, MPU:U$1.3, MPU:U$1.6, REG:C1.1, REG:L2.2, REG:U1.5, RTC:C1.1, RTC:R6.2, RTC:R40.2, RTC:U$5.3, S1.1
VS2: BT:C1.1, BT:C32.1, BT:U1.22, BT:U1.24, DP:C1.1, DP:C2.1, DP:C52.1, DP:C53.1, DP:U1.5, DP:U1.8, DP:U1.10, DP:U2.5, DP:U2.8, DP:U2.10, DP:U20.5, DP:U20.8, DP:U20.10, DP:U23.5, DP:U23.8, DP:U23.10, J4.P$3, S1.2, SEN1:C10.1, SEN1:C11.1, SEN1:C12.1, SEN1:C13.1, SEN1:C26.1, SEN1:C27.1, SEN1:C28.1, SEN1:C29.1, SEN1:C50.1, SEN1:U1.P$1, SEN1:U1.P$14, SEN1:U2.2, SEN1:U2.5, SEN1:U2.6, SEN1:U2.8, SEN1:U3.P$3, SEN1:U3.P$7, SEN1:U3.P$13, SEN1:U5.2, SEN1:U5.6, SEN1:U10.P$1, SEN2:C15.1, SEN2:C16.1, SEN2:C17.1, SEN2:C18.1, SEN2:C19.1, SEN2:C22.1, SEN2:C23.1, SEN2:C34.1, SEN2:C35.1, SEN2:C38.1, SEN2:C39.1, SEN2:C46.1, SEN2:C47.1, SEN2:C48.1, SEN2:U4.B1, SEN2:U4.C1, SEN2:U4.D1, SEN2:U5.P$1, SEN2:U5.P$5, SEN2:U5.P$16, SEN2:U7.P$2, SEN2:U7.P$8, SEN2:U8.P$1, SEN2:U8.P$14, SEN2:U9.P$5, SEN2:U13.P$10, SEN2:U13.P$11, SEN2:U16.P$1, SEN2:U16.P$6, SEN2:U16.P$10, U$1.A2, U$2.A2

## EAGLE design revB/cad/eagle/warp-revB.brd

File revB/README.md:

# Switch settings

## Power from USB and Sensors Enabled
```
S1.1 (top): on
S1.2: on
S1.3: off
S1.4: off

S2.1 (top): off
S2.2: off
S2.3: off
S2.4: on
``` 
## Power from Vias and Sensors Enabled
```
S1.1 (top): on
S1.2: on
S1.3: off
S1.4: off

S2.1 (top): off
S2.2: off
S2.3: off
S2.4: off
```

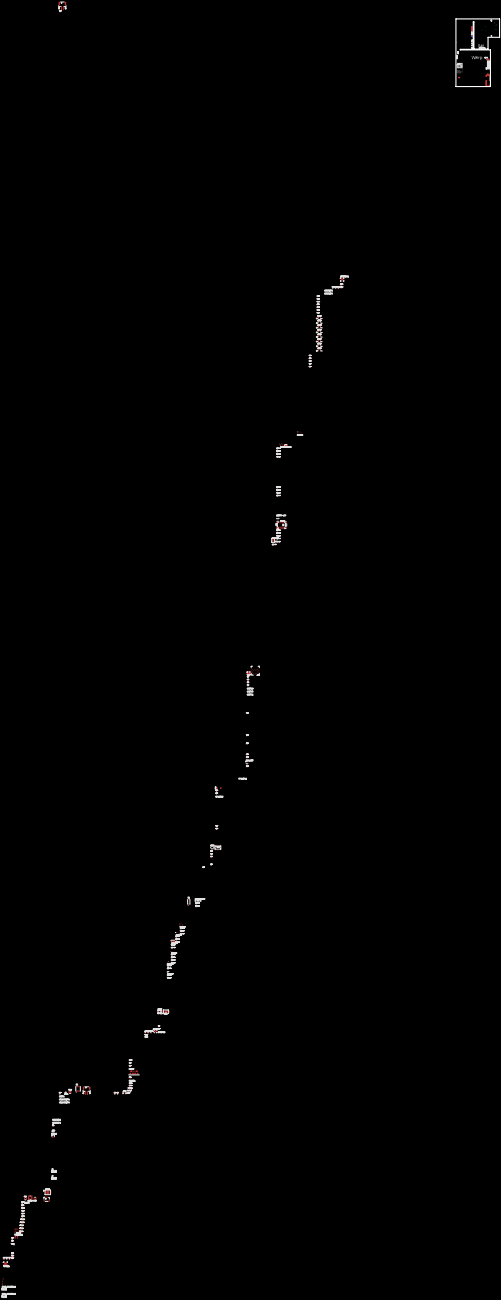
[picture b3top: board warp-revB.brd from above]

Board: 10 copper layers, 48.0 x 74.3 mm, 183 parts (0 on the bottom side), 89 nets.

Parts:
BOOST:C1, BOOST:C2, BOOST:C4, BOOST:C5, BOOST:C6, BOOST:C7, BOOST:C8, BOOST:C9: CPX3225A7552D; CPX3225A752D
BOOST:C42, BOOST:C44: 4.7uF; 0805
BOOST:C43: 0.1uF; 0603-CAP
BOOST:C45: 10nF; 0603-CAP
BOOST:C49: 22uF; 0805
BOOST:L2: 22uH; WE-TPC_3816
BOOST:L3: 10uH; WE-TPC_2811/2813_OLD
BOOST:R16: 4.02M; 0402-RES
BOOST:R17: 1.3M; 0402-RES
BOOST:R18: 6.49M; 0402-RES
BOOST:R19: 5.36M; 0402-RES
BOOST:R20: 9.09M; 0402-RES
BOOST:R21: 8.87M; 0402-RES
BOOST:R22: 4.22M; 0402-RES
BOOST:TP1, BOOST:TP2, BOOST:TP3, BOOST:TP4: TPSTP06R; TP06R
BOOST:U21: BQ25570PVQFN; BQ25570
CHARGER:C1: 1uF; 0805
CHARGER:C2, CHARGER:C3: 4.7uF; 0805
CHARGER:D1, CHARGER:D2: LED-0603
CHARGER:R1: 2.94k; 0402-RES
CHARGER:R2: 4.32k; 0402-RES
CHARGER:R3: 10k; 0402-RES
CHARGER:R4, CHARGER:R5: 4.7k; 0402-RES
CHARGER:R6: 56.2k; 0402-RES
CHARGER:TP1, CHARGER:TP2: TPSTP06R; TP06R
CHARGER:U$1: BQ24230VQFN; PVQFN-N16
DF40_SOCKETS:J1, DF40_SOCKETS:J2: DF40FC-20DP-0.4V(51)SOCKET; DF40C-20DP-0.4V(51)
FD1, FD2, FD3, FD4, FD5: FIDUCIAL1X2; FIDUCIAL-1X2
FPGA:C2: 4.7uF; 0805
FPGA:C3, FPGA:C13, FPGA:C14: 1uF; 0805
FPGA:C4, FPGA:C76, FPGA:C79: 10nF; 0402-CAP
FPGA:C5: 10uF; 0805
FPGA:C6, FPGA:C10, FPGA:C11, FPGA:C12: 0.1uF; 0603-CAP
FPGA:D1: BLUE; LED-0603
FPGA:L1: 2.2uH; WURTH-744025002
FPGA:R27: 100; 0402-RES
FPGA:R41: 4.7k; 0402-RES
FPGA:R42: DNP; 0402-RES
FPGA:R43: 10k; 0402-RES
FPGA:TP11: TPSTP06R; TP06R
FPGA:U$1: TPS62746DSBGA(8); DSBGA
FPGA:U$7: ICE40UP5K-UWG30; LATTICE-WLCSP-30
FT4222:C1: 4.7uF; 0805
FT4222:C2: 0.1uF; 0603-CAP
FT4222:C62: 0.47uF; 0402-CAP
FT4222:C63: 100pF; 0402-CAP
FT4222:C64, FT4222:C65: 27pF; 0402-CAP
FT4222:R5, FT4222:R8, FT4222:R9, FT4222:R23, FT4222:R25: 0402
FT4222:U18: FT4222H
FT4222:Y2: CS325
J1, J2: JST-2-SMD
J3: QIIC connector; 1X04_1MM_RA
J4, J5: DF40FC-20DP-0.4V(51); DF40C-20DP-0.4V(51)
MPU:C25, MPU:C31: 33pF; 0402-CAP
MPU:C36: 4.7uF (pol); 0402-CAP
MPU:C37, MPU:C51: 0.1uF; 0402-CAP
MPU:J1: CORTEX_DEBUG_SMD; SAMTECH_FTSH-105-01
MPU:R7, MPU:R11, MPU:R12: 10k; 0402-RES
MPU:R10: 4.7k; 0402-RES
MPU:S3: EVPAYG0BAEVPAYG0BA; EVPAYG0BA
MPU:TP25: TPSTP06R; TP06R
MPU:U1: MKL03Z32VFK4RQFN24; MKL03Z32VFK4R
MPU:U$1: AT45DB641E; UDFN
MPU:Y1: CM519-SMD; CM519
REG:C1, REG:C2: 10uF; 0805
REG:L2: WE-TPC_2828_OLD
REG:R14, REG:R15, REG:R44, REG:R45, REG:R46: 2M; 0402-RES
REG:U1: TPS6274XWSON; WSON-12
RF:C32, RF:C34: 0.1uF; 0402-CAP
RF:C33: 10uF; 0402-CAP
RF:C35: 22nF; 0402-CAP
RF:TP1, RF:TP2, RF:TP19, RF:TP20, RF:TP21: TPTP06R; TP06R
RF:U12: PAN1326C; PAN1326B
RF:U13: SI4705
RTC:C1: 0.1uF; 0603-CAP
RTC:D2: 250mA/100V; SOD-323
RTC:D3: BAS70-05; SOT23
RTC:R6, RTC:R40: 10k; 0402-RES
RTC:TP12: TPSTP06R; TP06R
RTC:U$5: RV-8803-C7_RTC; RV-C7
RTC:U$6: ML414_BATTERY_CONTACT; ML414
S1: CHS-02_SWITCH
S2: CHS-04_SWITCH
SENSORS-1:C3, SENSORS-1:C10, SENSORS-1:C12, SENSORS-1:C26, SENSORS-1:C28, SENSORS-1:C52, SENSORS-1:C53, SENSORS-2:C14, SENSORS-2:C16, SENSORS-2:C18, SENSORS-2:C20, SENSORS-2:C21, SENSORS-2:C23, SENSORS-2:C38, SENSORS-2:C46, SENSORS-2:C48: 0.1uF; 0402-CAP
SENSORS-1:C11, SENSORS-1:C13, SENSORS-1:C27, SENSORS-1:C29, SENSORS-2:C17, SENSORS-2:C22, SENSORS-2:C39, SENSORS-2:C47: 1uF; 0402-CAP
SENSORS-1:C30, SENSORS-2:C15: 10uF; 0402-CAP
SENSORS-1:C40: 2.2uF; 0402-CAP
SENSORS-1:C41: 1.0uF; 0402-CAP
SENSORS-1:C50, SENSORS-2:C19: 4.7uF; 0402-CAP
SENSORS-1:R4: 0402
SENSORS-1:U1: ADXL362
SENSORS-1:U2: BME680LGA; BME680
SENSORS-1:U3: BMX055
SENSORS-1:U10: TCS34725FN; TCS3772
SENSORS-1:U11: GRIDEYE; GRIDEYE-AMG88
SENSORS-1:U17: CCS811; LGA10
SENSORS-1:U20, SENSORS-1:U23: ISL23415UTQFN; ISL23415
SENSORS-2:C24: 10nF (25V); 0402-CAP
SENSORS-2:U4: HDC1000
SENSORS-2:U5: L3GD20H
SENSORS-2:U7: MAG3110
SENSORS-2:U8: MMA8451Q
SENSORS-2:U9: SI7021
SENSORS-2:U16: LPS25H
USB:C61: 4.7uF (pol); 0402-CAP
USB:C66: 0.1uF; 0402-CAP
USB:FB1: 600R/1A; 0603
USB:J7: ZX62-AB-5PA(31)MICRO-AB-SMT; ZX62-AB-5PA(31)
USB:TP1: TPSTP06R; TP06R

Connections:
ADXL362_FT4222_SPI_CS: FT4222:U18.P$17, J4.P$18, MPU:U1.P$15, SENSORS-1:U1.P$8
BAT: CHARGER:C3.1, CHARGER:TP1.TP, CHARGER:U$1.2, CHARGER:U$1.3, J1.2
BOOST:LBOOST: BOOST:L2.2, BOOST:U21.20
BOOST:LBUCK: BOOST:L3.1, BOOST:U21.16
BOOST:OK_HYST: BOOST:R17.1, BOOST:R19.2, BOOST:U21.10
BOOST:OK_PROG: BOOST:R18.2, BOOST:R19.1, BOOST:U21.11
BOOST:VBAT_OV: BOOST:R16.1, BOOST:R20.2, BOOST:U21.7
BOOST:VOUT_SET: BOOST:R21.1, BOOST:R22.2, BOOST:U21.12
BOOST:VRDIV: BOOST:R16.2, BOOST:R17.2, BOOST:R21.2, BOOST:U21.8
BOOST:VREF_SAMP: BOOST:C45.1, BOOST:U21.4
BOOST:VSTOR: BOOST:C42.1, BOOST:C43.1, BOOST:TP4.TP, BOOST:U21.3, BOOST:U21.6, BOOST:U21.19
BOOST_EN: BOOST:U21.5, S2.1', S2.2'
BOOST_VBAT: BOOST:C1.+, BOOST:C2.+, BOOST:C4.+, BOOST:C5.+, BOOST:C6.+, BOOST:C7.+, BOOST:C8.+, BOOST:C9.+, BOOST:TP3.TP, BOOST:U21.18, S2.2
BOOST_VOUT: BOOST:C49.1, BOOST:L3.2, BOOST:TP2.TP, BOOST:U21.14, S2.3
CHARGER:N$1: CHARGER:R2.2, CHARGER:U$1.16
CHARGER:N$2: CHARGER:R1.2, CHARGER:U$1.12
CHARGER:N$3: CHARGER:R4.1, CHARGER:U$1.7
CHARGER:N$4: CHARGER:R3.2, CHARGER:U$1.1
CHARGER:N$5: CHARGER:R5.1, CHARGER:U$1.9
CHARGER:N$6: CHARGER:D1.C, CHARGER:R4.2
CHARGER:N$7: CHARGER:D2.C, CHARGER:R5.2
CHARGER:N$8: CHARGER:R6.2, CHARGER:U$1.14
CHARGE_VOUT: CHARGER:C2.1, CHARGER:D1.A, CHARGER:D2.A, CHARGER:TP2.TP, CHARGER:U$1.10, CHARGER:U$1.11, S2.4
FPGA:CRESET_B: FPGA:R43.1, FPGA:U$7.F3
FPGA:ICE40_VCC_PLL: FPGA:C5.1, FPGA:C6.1, FPGA:R27.1, FPGA:U$7.B2
FPGA:IOB_0A: FPGA:D1.A, FPGA:U$7.E5
FPGA:N$1: FPGA:D1.C, FPGA:R41.1
FPGA:N$2: FPGA:L1.1, FPGA:U$1.A1
FPGA:VCC_1V2: FPGA:L1.2, FPGA:R27.2, FPGA:TP11.TP, FPGA:U$1.C2, FPGA:U$7.C2
FPGA_CS: FPGA:U$7.C1, MPU:U1.P$7
FPGA_VS: FPGA:C3.1, FPGA:C4.1, FPGA:C10.1, FPGA:C11.1, FPGA:C12.1, FPGA:C13.1, FPGA:C14.1, FPGA:C76.1, FPGA:C79.1, FPGA:R43.2, FPGA:U$1.B1, FPGA:U$7.A3, FPGA:U$7.C4, FPGA:U$7.D2, FPGA:U$7.D4, S1.1', S1.2'
FT4222:N$2: FT4222:R23.2, FT4222:U18.P$32
FT4222:N$3: FT4222:R8.2, FT4222:U18.P$2
FT4222:N$4: FT4222:C62.1, FT4222:R5.1, FT4222:U18.P$3
FT4222:N$5: FT4222:C63.1, FT4222:R9.2, FT4222:U18.P$21
FT4222:N$6: FT4222:C64.1, FT4222:R25.1, FT4222:U18.P$18, FT4222:Y2.3
FT4222:N$15: FT4222:C65.1, FT4222:R25.2, FT4222:U18.P$19, FT4222:Y2.1
GND: BOOST:C1.-, BOOST:C2.-, BOOST:C4.-, BOOST:C5.-, BOOST:C6.-, BOOST:C7.-, BOOST:C8.-, BOOST:C9.-, BOOST:C42.2, BOOST:C43.2, BOOST:C44.2, BOOST:C45.2, BOOST:C49.2, BOOST:R18.1, BOOST:R20.1, BOOST:R22.1, BOOST:U21.1, BOOST:U21.9, BOOST:U21.15, BOOST:U21.17, BOOST:U21.21, CHARGER:C1.2, CHARGER:C2.2, CHARGER:C3.2, CHARGER:R1.1, CHARGER:R2.1, CHARGER:R3.1, CHARGER:R6.1, CHARGER:U$1.4, CHARGER:U$1.6, CHARGER:U$1.8, CHARGER:U$1.15, CHARGER:U$1.EP, FPGA:C2.2, FPGA:C3.2, FPGA:C4.2, FPGA:C5.2, FPGA:C6.2, FPGA:C10.2, FPGA:C11.2, FPGA:C12.2, FPGA:C13.2, FPGA:C14.2, FPGA:C76.2, FPGA:C79.2, FPGA:R41.2, FPGA:R42.1, FPGA:U$1.B2, FPGA:U$1.C1, FPGA:U$7.B4, FPGA:U$7.E2, FT4222:C1.2, FT4222:C2.2, FT4222:C62.2, FT4222:C63.2, FT4222:C64.2, FT4222:C65.2, FT4222:R9.1, FT4222:U18.P$4, FT4222:U18.P$5, FT4222:U18.P$6, FT4222:U18.P$20, FT4222:U18.P$24, FT4222:U18.P$27, FT4222:U18.P$28, J1.1, J2.1, J3.1, J4.P$1, J5.P$1, MPU:C25.2, MPU:C31.2, MPU:C51.2, MPU:J1.3, MPU:J1.5, MPU:R12.2, MPU:S3.B, MPU:S3.B', MPU:U1.P$4, MPU:U1.P$PAD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
I2C0_SCL/UART_TX: FT4222:U18.P$13, J3.4, J4.P$11, MPU:U1.P$17, RF:U12.P$5, RTC:U$5.8
I2C0_SDA/UART_RX: FT4222:U18.P$14, J3.3, J4.P$12, MPU:U1.P$18, RF:U12.P$6, RTC:U$5.1
I2C1_SCL: FPGA:U$7.C3, J4.P$13, SENSORS-1:U2.4, SENSORS-1:U3.P$9, SENSORS-1:U10.P$2, SENSORS-1:U11.3, SENSORS-1:U17.10, SENSORS-1:U20.6
I2C1_SDA: FPGA:U$7.F4, J4.P$14, SENSORS-1:U2.3, SENSORS-1:U3.P$11, SENSORS-1:U10.P$6, SENSORS-1:U11.2, SENSORS-1:U17.9, SENSORS-1:U23.6
I2C2_SCL: FPGA:U$7.A2, J4.P$15, RF:U13.P$7, SENSORS-2:U4.A1, SENSORS-2:U5.P$2, SENSORS-2:U7.P$7, SENSORS-2:U8.P$4, SENSORS-2:U9.P$6, SENSORS-2:U16.P$2
I2C2_SDA: FPGA:U$7.A1, J4.P$16, RF:U13.P$8, SENSORS-2:U4.A2, SENSORS-2:U5.P$3, SENSORS-2:U7.P$6, SENSORS-2:U8.P$6, SENSORS-2:U9.P$1, SENSORS-2:U16.P$4
ISL23415_SPI_CS: J4.P$17, MPU:U1.P$20, SENSORS-1:U20.4, SENSORS-1:U23.4
KL03_CLKOUT32K: MPU:U1.P$21, RF:U12.P$8, RF:U13.P$9
MPU:AT45DB321F_SPI_CS: MPU:U1.P$16, MPU:U$1.4
MPU:EXTAL0: MPU:C31.1, MPU:U1.P$5, MPU:Y1.P$1
MPU:N$4: MPU:R7.1, MPU:U$1.5
MPU:XTAL0: MPU:C25.1, MPU:U1.P$6, MPU:Y1.P$2
unnamed: FT4222:U18.P$23, USB:J7.3
unnamed: FT4222:U18.P$22, USB:J7.2
PAN1326_!SHUTD: J4.P$20, MPU:U1.P$13, RF:U12.P$16
PV_VS: BOOST:C44.1, BOOST:L2.1, BOOST:TP1.TP, BOOST:U21.2, J2.2, J5.P$2
REG:SW: REG:L2.1, REG:U1.2
REG_CTRL: MPU:U1.P$19, REG:R14.2, REG:U1.4
REG_VIN: REG:C2.1, REG:U1.1, REG:U1.12, S2.3', S2.4'
REG_VSEL1: MPU:U1.P$1, REG:R44.2, REG:U1.11
REG_VSEL2: MPU:U1.P$2, REG:R45.2, REG:U1.10
REG_VSEL3: MPU:U1.P$9, REG:R46.2, REG:U1.9
REG_VSEL4: MPU:U1.P$10, REG:R15.2, REG:U1.8
RF:PAN1326_AUD_CLK: RF:U12.P$19, RF:U13.P$17
RF:PAN1326_AUD_FSYNC: RF:U12.P$7, RF:U13.P$16
RF:PAN1326_AUD_IN: RF:U12.P$18, RF:U13.P$15
RF:PAN1326_AUD_OUT: RF:TP20.TP, RF:U12.P$17
RF:PAN1326_RF: RF:TP21.TP, RF:U12.P$13
RF:PAN1326_TX_DBG: RF:TP19.TP, RF:U12.P$2
RF:SI4705_LPI: RF:TP1.TP, RF:U13.P$4
RTC:N$1: RTC:C1.1, RTC:D2.C, RTC:D3.3, RTC:U$5.3
RTC:N$3: RTC:R6.1, RTC:U$5.7
RTC:VBB: RTC:D2.A, RTC:TP12.TP, RTC:U$6.1, RTC:U$6.3
RTC_!INT!/RESET_B: J4.P$7, J5.P$5, MPU:J1.10, MPU:R10.1, MPU:S3.A, MPU:S3.A', MPU:U1.P$23, RTC:R40.1, RTC:U$5.6
SENSORS-1:N$7: SENSORS-1:U17.4, SENSORS-1:U17.5
SENSORS-2:N$1: SENSORS-2:C14.1, SENSORS-2:U8.P$2
SENSORS-2:N$6: SENSORS-2:C46.2, SENSORS-2:C47.2
SENSORS-2:N$12: SENSORS-2:C15.2, SENSORS-2:C48.2
SENSORS-2:N$17: SENSORS-2:C20.1, SENSORS-2:C21.1, SENSORS-2:U7.P$1, SENSORS-2:U7.P$4
SENSORS-2:N$18: SENSORS-2:C38.2, SENSORS-2:C39.2
SI4705_!RST!: J4.P$19, MPU:U1.P$14, RF:U13.P$5
SI4705_FMI: J5.P$6, RF:TP2.TP, RF:U13.P$2
SPI_MISO/UART_RTS: FPGA:U$7.F1, FT4222:U18.P$9, J4.P$9, MPU:U1.P$11, MPU:U$1.1, RF:U12.P$4, SENSORS-1:U1.P$7, SENSORS-1:U20.2, SENSORS-1:U23.2
SPI_MOSI/UART_CTS: FPGA:U$7.E1, FT4222:U18.P$10, J4.P$10, MPU:U1.P$8, MPU:U$1.8, RF:U12.P$3, SENSORS-1:U1.P$6, SENSORS-1:U20.3, SENSORS-1:U23.3
SPI_SCK: FPGA:U$7.D1, FT4222:U18.P$8, J4.P$8, MPU:U1.P$12, MPU:U$1.2, SENSORS-1:U1.P$4, SENSORS-1:U20.1, SENSORS-1:U23.1
SWD_CLK: J4.P$6, J5.P$4, MPU:J1.4, MPU:R12.1, MPU:U1.P$22
SWD_DIO: J4.P$5, J5.P$3, MPU:J1.2, MPU:R11.1, MPU:U1.P$24
USB:VBUS: USB:FB1.2, USB:J7.1
USB_5V: CHARGER:C1.1, CHARGER:U$1.13, FPGA:C2.1, FPGA:U$1.A2, FT4222:C1.1, FT4222:C2.1, FT4222:U18.P$26, FT4222:U18.P$30, J4.P$2, USB:C61.1, USB:C66.1, USB:FB1.1, USB:TP1.TP
VS_PRI: FT4222:R5.2, FT4222:R8.1, FT4222:R23.1, FT4222:U18.P$1, FT4222:U18.P$7, J4.P$4, MPU:C36.1, MPU:C37.1, MPU:C51.1, MPU:J1.1, MPU:R7.2, MPU:R10.2, MPU:R11.2, MPU:TP25.TP, MPU:U1.P$3, MPU:U$1.3, MPU:U$1.6, REG:C1.1, REG:L2.2, REG:U1.5, RTC:D3.1, RTC:D3.2, RTC:R6.2, RTC:R40.2, S1.1
VS_SEC: J4.P$3, REG:U1.6, RF:C32.1, RF:C33.1, RF:C34.1, RF:C35.1, RF:U12.P$10, RF:U12.P$11, RF:U12.P$15, RF:U12.P$22, RF:U13.P$10, RF:U13.P$11, S1.2, SENSORS-1:C3.1, SENSORS-1:C10.1, SENSORS-1:C11.1, SENSORS-1:C12.1, SENSORS-1:C13.1, SENSORS-1:C26.1, SENSORS-1:C27.1, SENSORS-1:C28.1, SENSORS-1:C29.1, SENSORS-1:C30.1, SENSORS-1:C40.1, SENSORS-1:C50.1, SENSORS-1:C52.1, SENSORS-1:C53.1, SENSORS-1:U1.P$1, SENSORS-1:U1.P$14, SENSORS-1:U2.2, SENSORS-1:U2.5, SENSORS-1:U2.6, SENSORS-1:U2.8, SENSORS-1:U3.P$3, SENSORS-1:U3.P$7, SENSORS-1:U3.P$13, SENSORS-1:U10.P$1, SENSORS-1:U11.9, SENSORS-1:U11.12, SENSORS-1:U11.13, SENSORS-1:U17.2, SENSORS-1:U17.6, SENSORS-1:U20.5, SENSORS-1:U20.8, SENSORS-1:U20.10, SENSORS-1:U23.5, SENSORS-1:U23.8, SENSORS-1:U23.10, SENSORS-2:C15.1, SENSORS-2:C16.1, SENSORS-2:C17.1, SENSORS-2:C18.1, SENSORS-2:C19.1, SENSORS-2:C22.1, SENSORS-2:C23.1, SENSORS-2:C24.1, SENSORS-2:C38.1, SENSORS-2:C39.1, SENSORS-2:C46.1, SENSORS-2:C47.1, SENSORS-2:C48.1, SENSORS-2:U4.B1, SENSORS-2:U4.C1, SENSORS-2:U4.D1, SENSORS-2:U5.P$1, SENSORS-2:U5.P$14, SENSORS-2:U5.P$16, SENSORS-2:U7.P$2, SENSORS-2:U7.P$8, SENSORS-2:U8.P$1, SENSORS-2:U8.P$14, SENSORS-2:U9.P$5, SENSORS-2:U16.P$1, SENSORS-2:U16.P$6, SENSORS-2:U16.P$10

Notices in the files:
parts and their libraries:
SparkFun-Passives: Licensing: Creative Commons ShareAlike 4.0 International - https://creativecommons.org/licenses/by-sa/4.0
EMCComponents: Copyright: Würth Elektronik
